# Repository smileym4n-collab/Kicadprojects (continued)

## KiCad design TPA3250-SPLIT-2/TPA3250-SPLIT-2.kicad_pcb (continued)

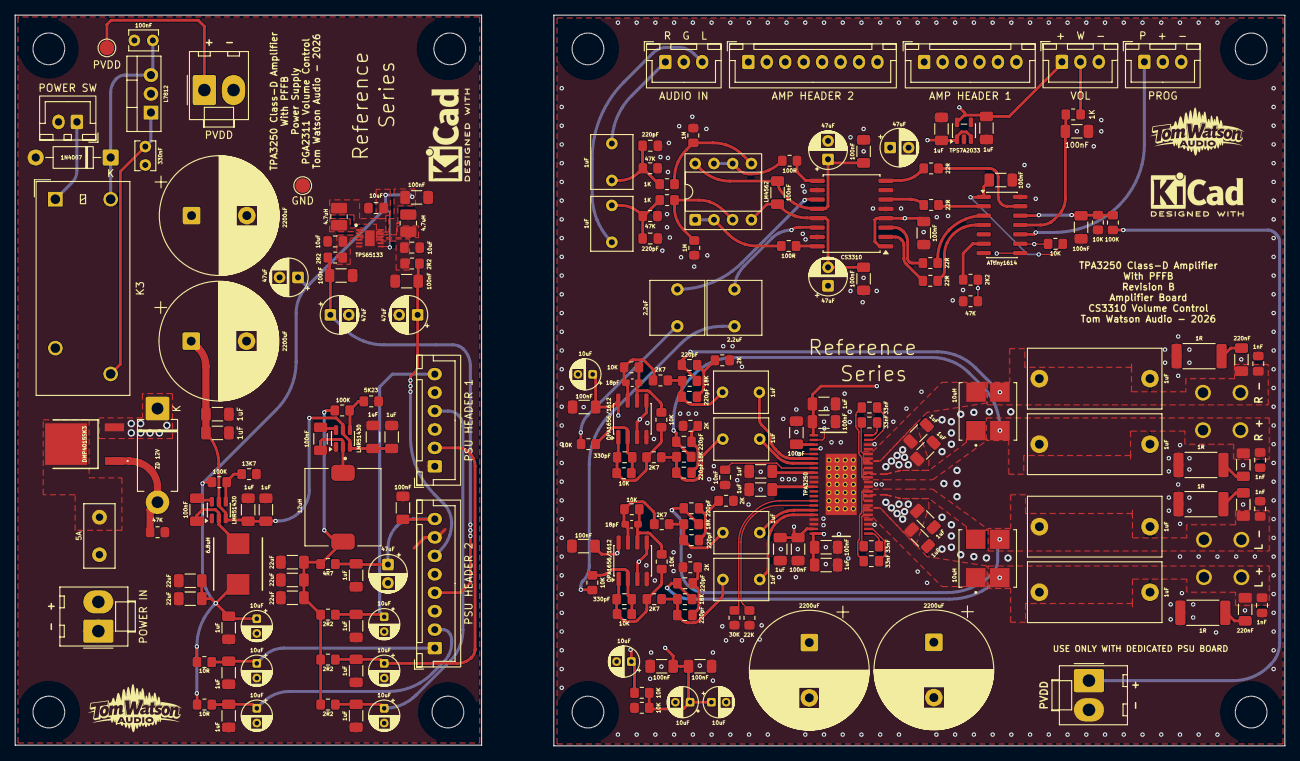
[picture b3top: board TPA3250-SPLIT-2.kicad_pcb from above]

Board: 4 copper layers, 172.1 x 99.1 mm, 221 parts (0 on the bottom side), 111 nets.

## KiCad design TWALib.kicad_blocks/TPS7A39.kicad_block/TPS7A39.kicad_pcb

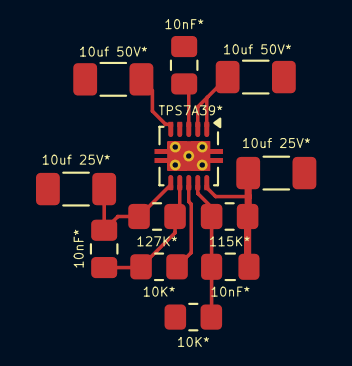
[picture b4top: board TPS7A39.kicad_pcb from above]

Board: 2 copper layers, 12 parts (0 on the bottom side), 9 nets.

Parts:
C59, C65, C70: 10nF*; C_0805_2012Metric_Pad1.18x1.45mm_HandSolder
C73, C78: 10uf 25V*; C_1206_3216Metric_Pad1.33x1.80mm_HandSolder
C79, C80: 10uf 50V*; C_1206_3216Metric_Pad1.33x1.80mm_HandSolder
R43, R56: 10K*; R_0805_2012Metric_Pad1.20x1.40mm_HandSolder
R57: 115K*; R_0805_2012Metric_Pad1.20x1.40mm_HandSolder
R58: 127K*; R_0805_2012Metric_Pad1.20x1.40mm_HandSolder
U7: TPS7A39*; Texas_S-PVSON-N10_ThermalVias

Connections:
/LM1875/VCC: C79.1, U7.1 (INP), U7.2 (EN)
/LM1875/VEE: C80.1, U7.5 (INN)
/POWER/+15V: C59.1, C73.1, R57.1, U7.10 (OUTP)
/POWER/-15V: C65.2, C78.1, R58.2, U7.6 (OUTN)
GND: C70.2, C73.2, C78.2, C79.2, C80.2, R56.2, U7.4 (GND), U7.11 (GND)
unnamed: R43.1, U7.8 (BUF)
unnamed: C65.1, R43.2, R58.1, U7.7 (FBN)
unnamed: C59.2, R56.1, R57.2, U7.9 (FBP)
unnamed: C70.1, U7.3 (NR/SS)
